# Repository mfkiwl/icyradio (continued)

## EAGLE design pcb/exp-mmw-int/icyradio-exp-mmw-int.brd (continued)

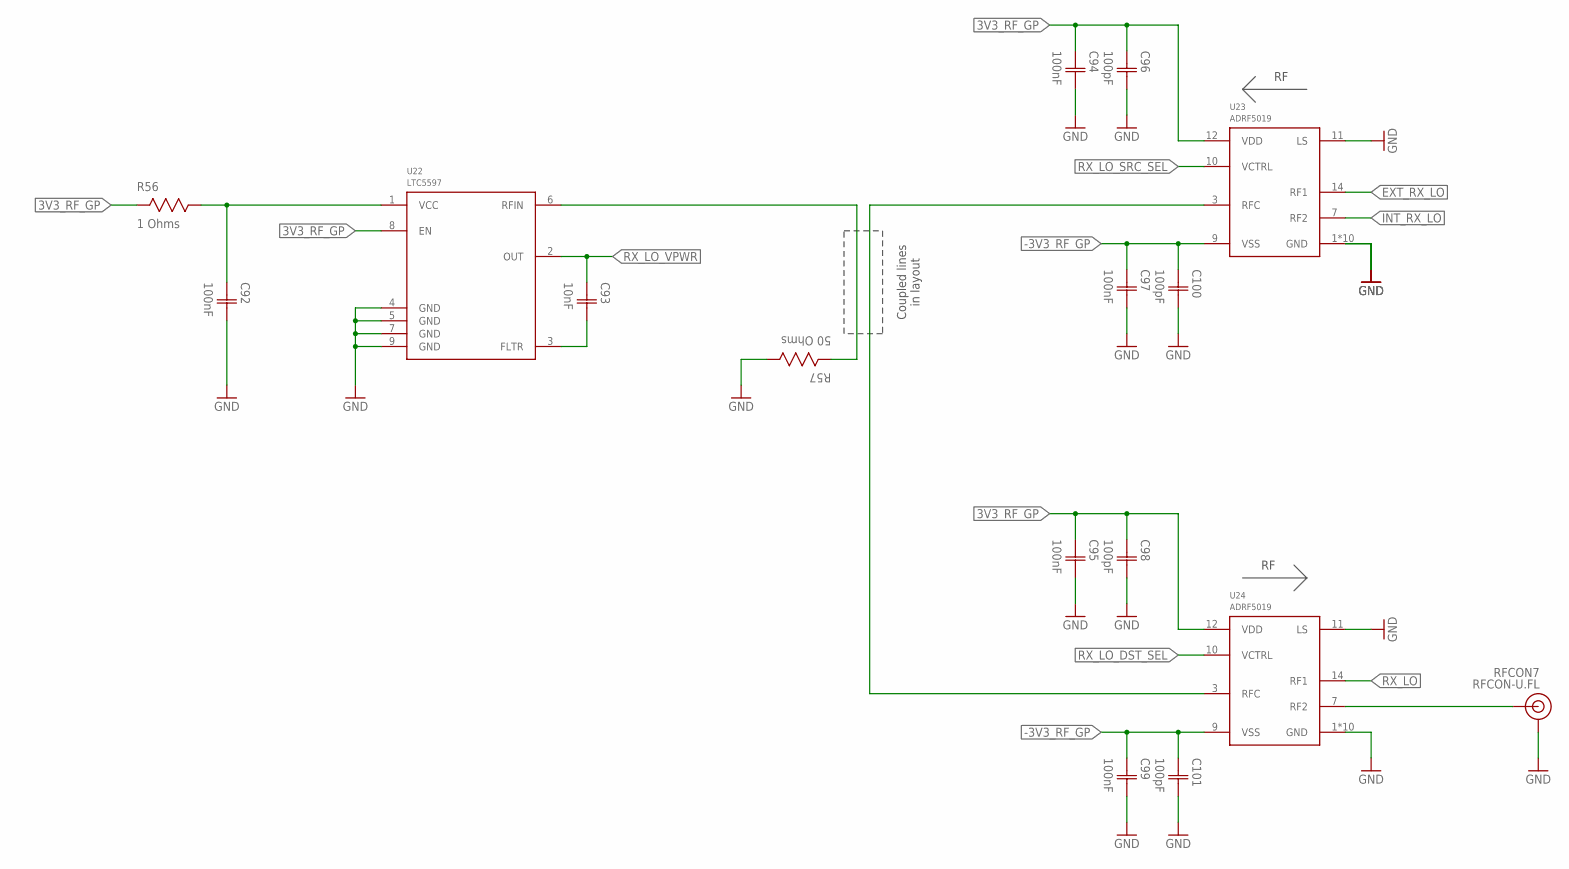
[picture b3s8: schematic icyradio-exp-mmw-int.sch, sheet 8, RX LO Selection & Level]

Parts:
C92, C94, C95, C97, C99: 100nF; CAP0402
C93: 10nF; CAP0402
C96, C98, C100, C101: 100pF; CAP0402
R56: 1 Ohms; RES0402
R57: 50 Ohms; RES0402
RFCON7: RFCON-U.FL; U.FL
U22: LTC5597; DFN8_2X2
U23, U24: ADRF5019; LFCSP16

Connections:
3V3_RF_GP: C94.1 (C1), C95.1 (C1), C96.1 (C1), C98.1 (C1), R56.2, U22.8 (EN), U23.12 (VDD), U24.12 (VDD); also elsewhere on the board
-3V3_RF_GP: C97.1 (C1), C99.1 (C1), C100.1 (C1), C101.1 (C1), U23.9 (VSS), U24.9 (VSS); also elsewhere on the board
EXT_RX_LO: U23.14 (RF1); also elsewhere on the board
GND: C92.2 (C2), C94.2 (C2), C95.2 (C2), C96.2 (C2), C97.2 (C2), C98.2 (C2), C99.2 (C2), C100.2 (C2), C101.2 (C2), R57.1, RFCON7.P$1 (GND), RFCON7.P$2 (GND), U22.4 (GND), U22.5 (GND), U22.7 (GND), U22.9 (GND), U23.1 (GND), U23.2 (GND), U23.4 (GND), U23.5 (GND), U23.6 (GND), U23.8 (GND), U23.11 (LS), U23.13 (GND), U23.15 (GND), U23.16 (GND), U23.17 (GND), U24.1 (GND), U24.2 (GND), U24.4 (GND), U24.5 (GND), U24.6 (GND), U24.8 (GND), U24.11 (LS), U24.13 (GND), U24.15 (GND), U24.16 (GND), U24.17 (GND); also elsewhere on the board
INT_RX_LO: U23.7 (RF2); also elsewhere on the board
unnamed: C93.2 (C2), U22.3 (FLTR)
unnamed: C92.1 (C1), R56.1, U22.1 (VCC)
RX_LO: U24.14 (RF1); also elsewhere on the board
RX_LO_DST_SEL: U24.10 (VCTRL); also elsewhere on the board
RX_LO_MON: RFCON7.P$3 (SIGNAL), U24.7 (RF2)
RX_LO_SNS: R57.2, U22.6 (RFIN)
RX_LO_SRC_SEL: U23.10 (VCTRL); also elsewhere on the board
RX_LO_VPWR: C93.1 (C1), U22.2 (OUT); also elsewhere on the board
SEL_RX_LO: U23.3 (RFC), U24.3 (RFC)

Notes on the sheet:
Coupled lines in layout

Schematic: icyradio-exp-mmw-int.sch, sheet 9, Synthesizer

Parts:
C102, C103, C104, C105, C106, C107, C108, C110, C111: 100nF; CAP0402
C109, C112, C113, C114, C115: 22uF; CAP0402
C116, C117: 1uF; CAP0402
C118, C120, C121, C124, C125, C126, C127: 10nF; CAP0402
C119: 2.2nF; CAP0402
C122, C123: 10pF; CAP0402
FB3: 1uH; IND0603
L5, L6: 18nH; IND0402
R58: 49.9 Ohms; RES0402
R59, R60, R61, R62: 1K Ohms; RES0402
R63: 20 Ohms; RES0402
R64: 62 Ohms; RES0402
R65, R66, R67, R68, R69, R70: 50 Ohms; RES0402
U25: 8V97003; VFQFPN48

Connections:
3V3_SYNTH: C103.1 (C1), C104.1 (C1), C105.1 (C1), C107.1 (C1), C108.1 (C1), C110.1 (C1), C111.1 (C1), FB3.1, L5.1, L6.1, R59.2, R61.2, U25.3 (VDDVCO2), U25.12 (VDDPDCP), U25.15 (VDDFB), U25.24 (VDDIN), U25.33 (VDDVCO1), U25.37 (VDDOUTA), U25.48 (VDDOUTB); also elsewhere on the board
!SYNTH_RESET: U25.31 (!RESET); also elsewhere on the board
!SYNTH_SPI_CS: U25.25 (!CS); also elsewhere on the board
GND: C103.2 (C2), C104.2 (C2), C105.2 (C2), C106.2 (C2), C107.2 (C2), C108.2 (C2), C109.2 (C2), C110.2 (C2), C111.2 (C2), C112.2 (C2), C113.2 (C2), C114.2 (C2), C115.2 (C2), C116.2 (C2), C117.2 (C2), C118.2 (C2), C119.2 (C2), C120.2 (C2), C121.2 (C2), C122.2 (C2), C123.2 (C2), R58.1, R60.1, R62.1, R69.1, R70.1, U25.14 (VSSPDCP), U25.17 (VSSFB), U25.19 (VSSDIG), U25.20 (VSSIN), U25.38 (VSSOUTA), U25.41 (VSSOUTA), U25.44 (VSSOUTB), U25.47 (VSSOUTB), U25.49 (VSS); also elsewhere on the board
INT_RX_LO: C127.2 (C2); also elsewhere on the board
INT_TX_LO: C126.2 (C2); also elsewhere on the board
unnamed: C117.1 (C1), R63.1
SYNTH_CE: U25.29 (CE); also elsewhere on the board
SYNTH_CPBIAS: C115.1 (C1), U25.11 (CPBIAS)
SYNTH_CPOUT: C118.1 (C1), R63.2, R64.2, U25.10 (CPOUT)
SYNTH_LD: U25.8 (LD); also elsewhere on the board
SYNTH_MUTE: U25.7 (MUTE); also elsewhere on the board
SYNTH_REFIN_N: C106.1 (C1), R61.1, R62.2, U25.23 (!REF_IN)
SYNTH_REFIN_P: C102.2 (C2), R59.1, R60.2, U25.22 (REF_IN)
SYNTH_REF_CLK: C102.1 (C1), R58.2; also elsewhere on the board
SYNTH_RFOUTA_ACC_N: C124.2 (C2), R69.2
SYNTH_RFOUTA_BIAS: C120.1 (C1), C122.1 (C1), L5.2, R65.2, R67.2
SYNTH_RFOUTA_N: C124.1 (C1), R67.1, U25.39 (!RF_OUTA)
SYNTH_RFOUTA_P: C126.1 (C1), R65.1, U25.40 (RF_OUTA)
SYNTH_RFOUTB_ACC_N: C125.2 (C2), R70.2
SYNTH_RFOUTB_BIAS: C121.1 (C1), C123.1 (C1), L6.2, R66.2, R68.2
SYNTH_RFOUTB_N: C125.1 (C1), R68.1, U25.46 (!RF_OUTB)
SYNTH_RFOUTB_P: C127.1 (C1), R66.1, U25.45 (RF_OUTB)
SYNTH_SPI_MISO: U25.27 (SDO); also elsewhere on the board
SYNTH_SPI_MOSI: U25.28 (SDIO); also elsewhere on the board
SYNTH_SPI_SCK: U25.26 (SCLK); also elsewhere on the board
SYNTH_SYNC: U25.30 (SYNC); also elsewhere on the board
SYNTH_VDDDIG: C116.1 (C1), FB3.2, U25.18 (VDDDIG)
SYNTH_VREFVCO1: C113.1 (C1), U25.35 (VREFVCO1)
SYNTH_VREFVCO2: C114.1 (C1), U25.1 (VREFVCO2)
SYNTH_VREGVCO1: C109.1 (C1), U25.32 (VREGVCO1)
SYNTH_VREGVCO2: C112.1 (C1), U25.4 (VREGVCO2)
SYNTH_VTUNE: C119.1 (C1), R64.1, U25.5 (VTUNE)

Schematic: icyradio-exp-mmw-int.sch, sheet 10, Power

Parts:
C128: 10uF; CAP0603
C129, C130, C131, C137, C138, C139, C143, C145: 1uF; CAP0402
C132, C133, C134, C144, C147: 100nF; CAP0402
C135, C136: 10nF; CAP0402
C140, C141, C142, C146: 10uF; CAP0402
C148: 10pF; CAP0402
R71, R72, R73: 10K Ohms; RES0402
U26: ADP7142AUJZ-3.3; SOT23-5
U27: ADM7170ACPZ-5.0; LFCSP8_3X3
U28: ADM7172ACPZ-3.3; LFCSP8_3X3
U29: ADM8828; SOT23-6

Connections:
3V3_RF_GP: C137.1 (C1), C140.1 (C1), C143.1 (C1), C144.1 (C1), U26.4 (SENSE/ADJ), U26.5 (VOUT), U29.2 (IN); also elsewhere on the board
3V3_SYNTH: C139.1 (C1), C142.1 (C1), U28.1 (VOUT), U28.2 (VOUT), U28.3 (SENSE); also elsewhere on the board
5V0: C128.1 (C1), C129.1 (C1), C130.1 (C1), C131.1 (C1), C132.1 (C1), C133.1 (C1), C134.1 (C1), U26.1 (VIN), U27.7 (VIN), U27.8 (VIN), U28.7 (VIN), U28.8 (VIN); also elsewhere on the board
5V0_RF_LO: C138.1 (C1), C141.1 (C1), U27.1 (VOUT), U27.2 (VOUT), U27.3 (SENSE); also elsewhere on the board
-3V3_RF_GP: C146.1 (C1), C147.1 (C1), C148.1 (C1), U29.1 (OUT); also elsewhere on the board
GND: C128.2 (C2), C129.2 (C2), C130.2 (C2), C131.2 (C2), C132.2 (C2), C133.2 (C2), C134.2 (C2), C135.2 (C2), C136.2 (C2), C137.2 (C2), C138.2 (C2), C139.2 (C2), C140.2 (C2), C141.2 (C2), C142.2 (C2), C143.2 (C2), C144.2 (C2), C146.2 (C2), C147.2 (C2), C148.2 (C2), R71.1, R72.1, R73.1, U26.2 (GND), U27.6 (GND), U27.9 (GND), U28.6 (GND), U28.9 (GND), U29.4 (GND), U29.5 (SHDN); also elsewhere on the board
LO_ANA_PWR_EN: R71.2, U27.5 (EN); also elsewhere on the board
unnamed: C135.1 (C1), U27.4 (SS)
unnamed: C136.1 (C1), U28.4 (SS)
unnamed: C145.1 (C1), U29.6 (C+)
unnamed: C145.2 (C2), U29.3 (C-)
RF_GP_PWR_EN: R73.2, U26.3 (EN); also elsewhere on the board
SYNTH_PWR_EN: R72.2, U28.5 (EN); also elsewhere on the board

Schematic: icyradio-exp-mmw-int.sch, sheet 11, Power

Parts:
C149, C162: 10uF; CAP0603
C150, C151, C152, C156, C157, C158, C163, C164, C169, C170: 1uF; CAP0402
C153, C154, C155, C165, C166: 100nF; CAP0402
C159, C160, C161, C171, C172: 10uF; CAP0402
C167, C168: 10nF; CAP0402
JP3: PINHD-2X3; 2X03
R74: 0 Ohms; RES0402
R75, R76, R77, R78: 10K Ohms; RES0402
U30, U31: ADP7142AUJZ-1.8; SOT23-5
U32: ADP7102ACPZ-1.5; LFCSP8_3X3
U33, U34: ADM7171ACPZ-3.3; LFCSP8_3X3

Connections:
1V5_RF_RX: C158.1 (C1), C161.1 (C1), U32.1 (VOUT), U32.2 (SENSE); also elsewhere on the board
1V8_RF_RX: C157.1 (C1), C160.1 (C1), R74.2, U31.4 (SENSE/ADJ), U31.5 (VOUT); also elsewhere on the board
1V8_RF_TX: C156.1 (C1), C159.1 (C1), R74.1, U30.4 (SENSE/ADJ), U30.5 (VOUT); also elsewhere on the board
2V5: JP3.2
3V3: C149.1 (C1), C150.1 (C1), C151.1 (C1), C153.1 (C1), C154.1 (C1), JP3.1, U30.1 (VIN), U31.1 (VIN); also elsewhere on the board
3V3_RF_RX: C170.1 (C1), C172.1 (C1), U34.1 (VOUT), U34.2 (VOUT), U34.3 (SENSE); also elsewhere on the board
3V3_RF_TX: C169.1 (C1), C171.1 (C1), U33.1 (VOUT), U33.2 (VOUT), U33.3 (SENSE); also elsewhere on the board
5V0: C152.1 (C1), C155.1 (C1), C162.1 (C1), C163.1 (C1), C164.1 (C1), C165.1 (C1), C166.1 (C1), JP3.5, JP3.6, U32.8 (VIN), U33.7 (VIN), U33.8 (VIN), U34.7 (VIN), U34.8 (VIN); also elsewhere on the board
GND: C149.2 (C2), C150.2 (C2), C151.2 (C2), C152.2 (C2), C153.2 (C2), C154.2 (C2), C155.2 (C2), C156.2 (C2), C157.2 (C2), C158.2 (C2), C159.2 (C2), C160.2 (C2), C161.2 (C2), C162.2 (C2), C163.2 (C2), C164.2 (C2), C165.2 (C2), C166.2 (C2), C167.2 (C2), C168.2 (C2), C169.2 (C2), C170.2 (C2), C171.2 (C2), C172.2 (C2), JP3.3, JP3.4, R75.1, R76.1, R77.1, R78.1, U30.2 (GND), U31.2 (GND), U32.3 (GND), U32.6 (GND), U32.9 (GND), U33.6 (GND), U33.9 (GND), U34.6 (GND), U34.9 (GND); also elsewhere on the board
unnamed: C168.1 (C1), U34.4 (SS)
unnamed: C167.1 (C1), U33.4 (SS)
RX_ANA_PWR_EN: R75.2, U32.5 (EN/UVLO), U34.5 (EN); also elsewhere on the board
RX_DIG_PWR_EN: R77.2, U31.3 (EN); also elsewhere on the board
TX_ANA_PWR_EN: R76.2, U33.5 (EN); also elsewhere on the board
TX_DIG_PWR_EN: R78.2, U30.3 (EN); also elsewhere on the board

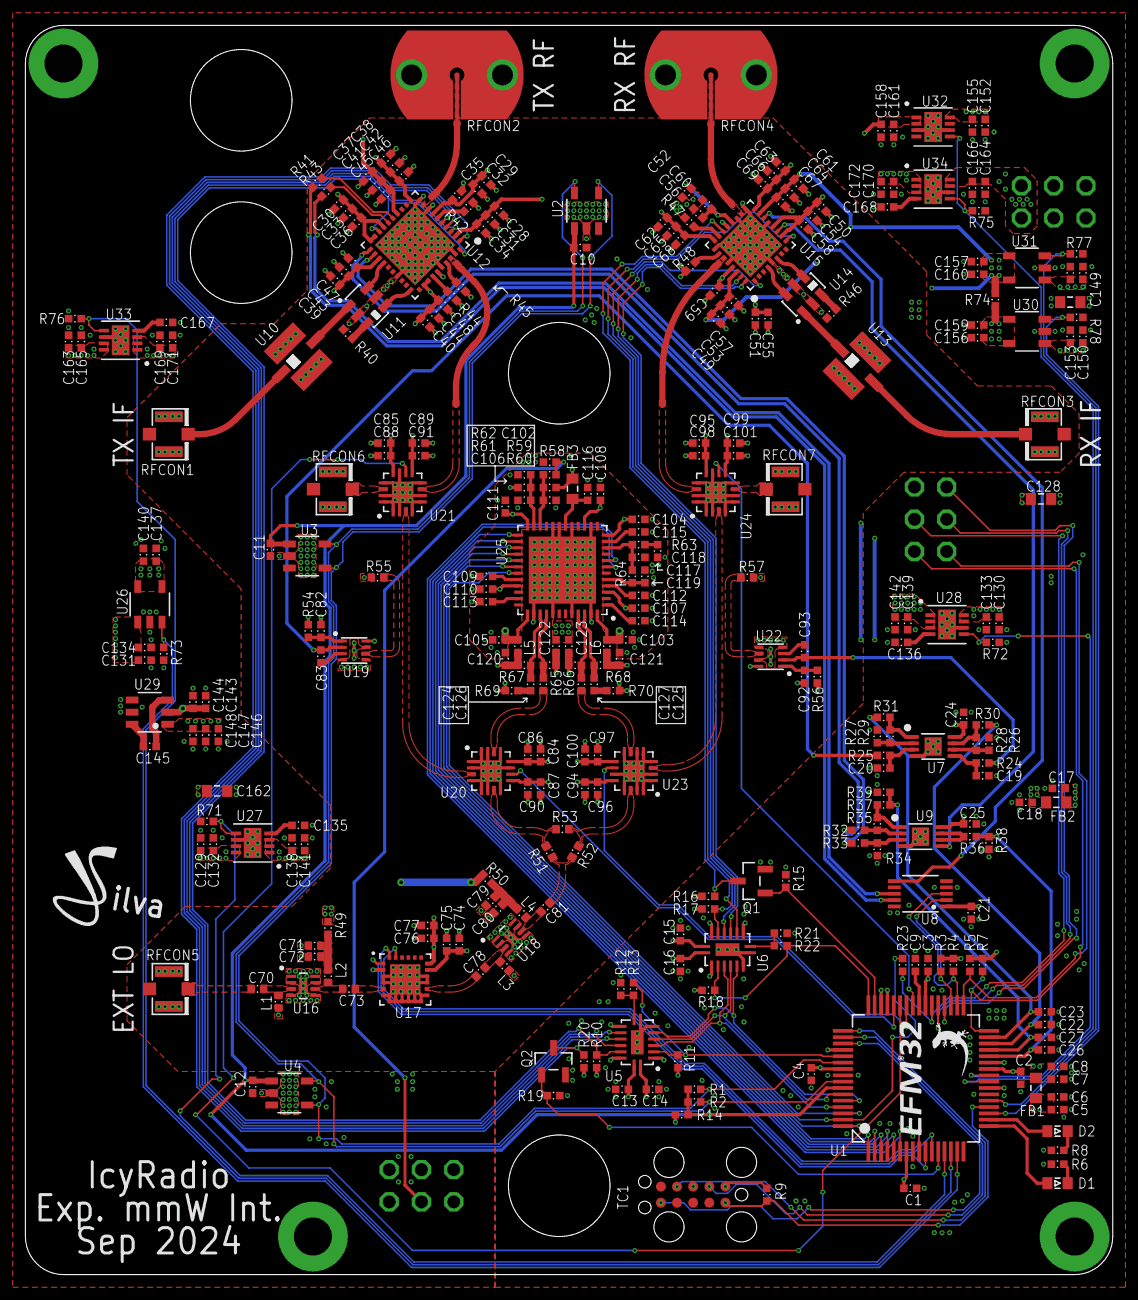
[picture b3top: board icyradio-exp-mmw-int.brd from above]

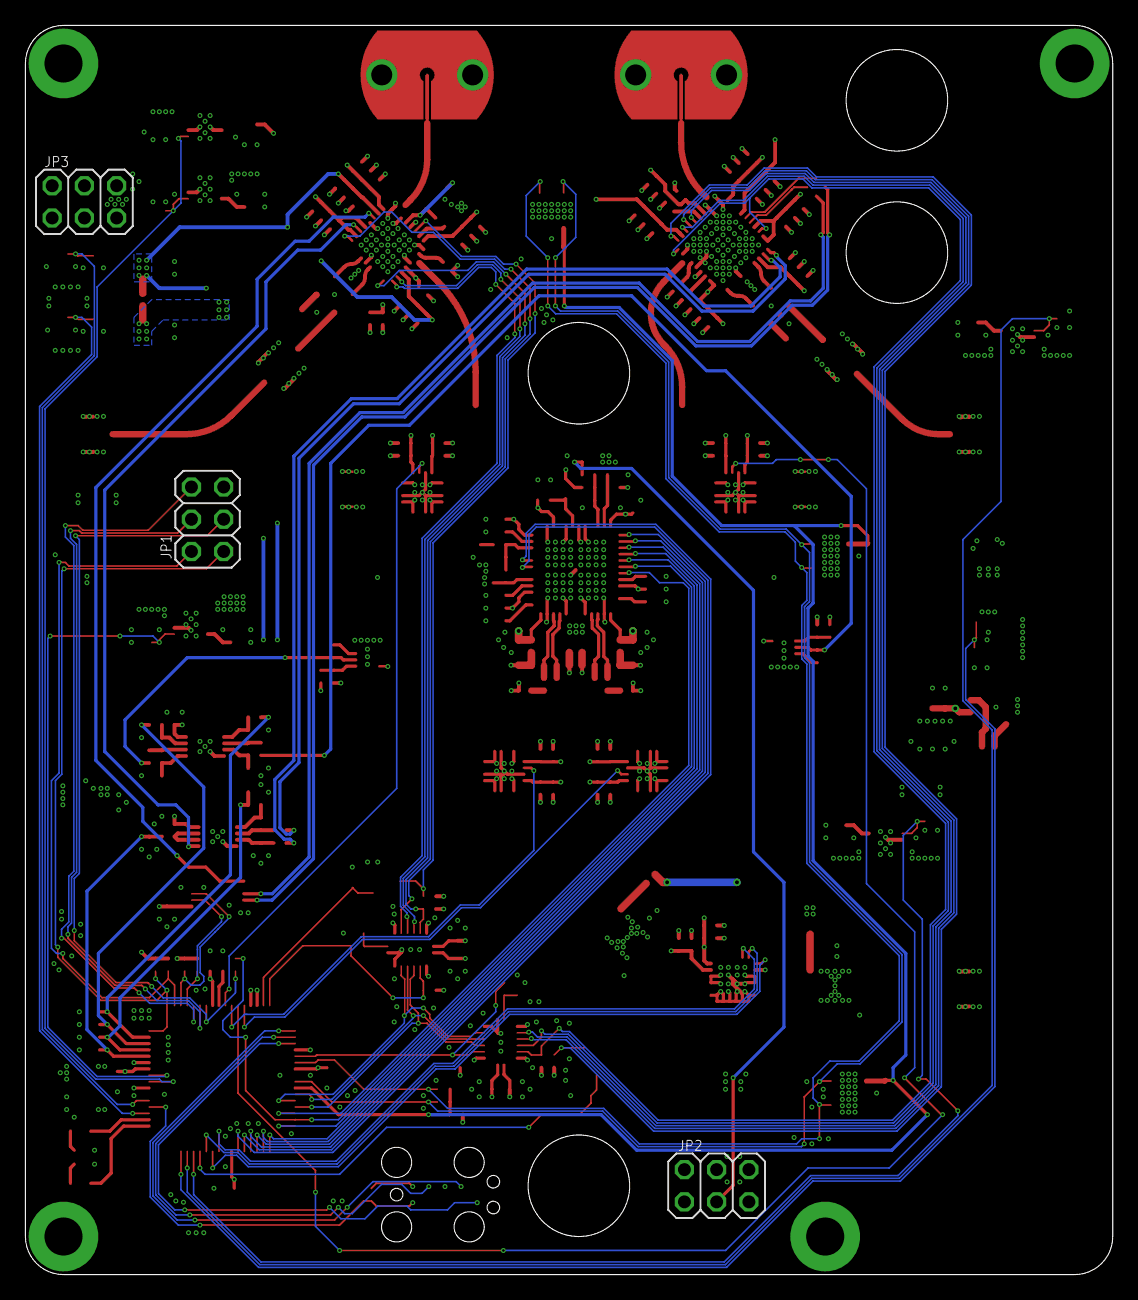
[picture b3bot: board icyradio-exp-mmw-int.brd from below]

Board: 4 copper layers, 85.7 x 98.4 mm, 309 parts (3 on the bottom side), 168 nets.

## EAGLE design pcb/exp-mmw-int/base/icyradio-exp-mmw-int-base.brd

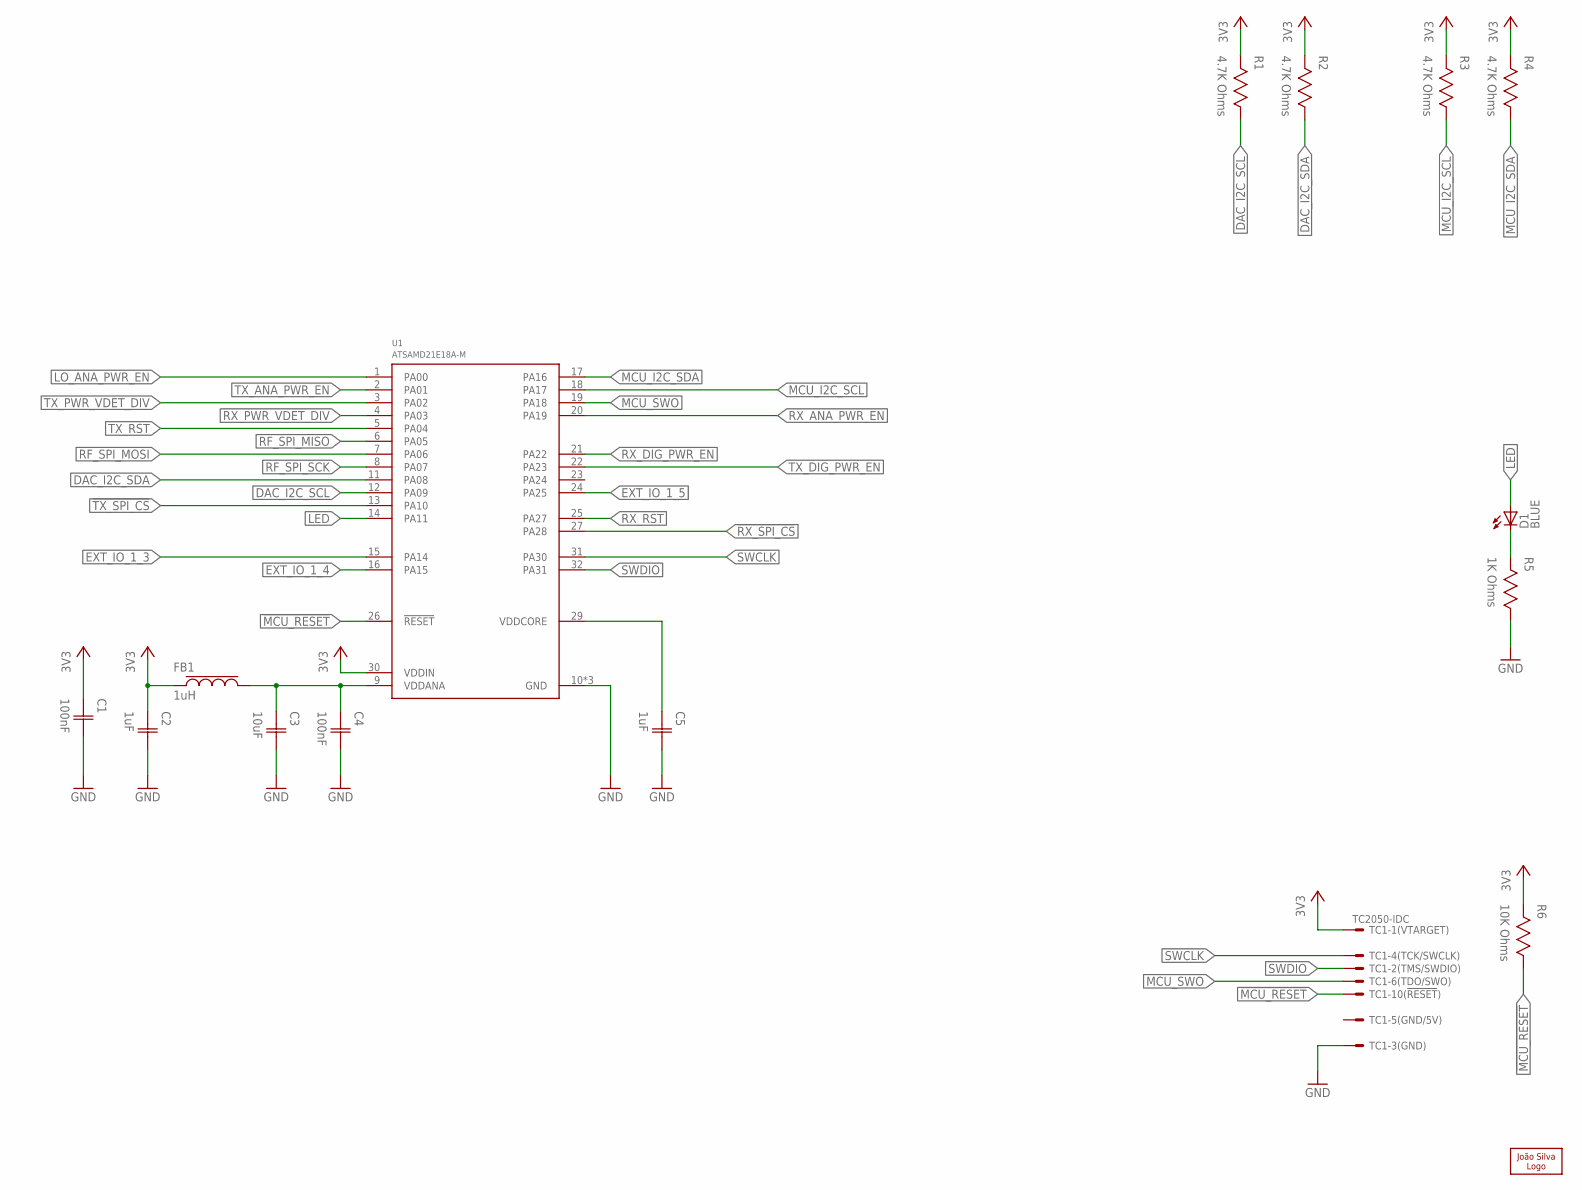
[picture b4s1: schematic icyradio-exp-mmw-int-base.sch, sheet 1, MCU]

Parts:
C1, C4: 100nF; CAP0402
C2, C5: 1uF; CAP0402
C3: 10uF; CAP0402
D1: LED0603; 0603
FB1: 1uH; IND0603
LOGO1: JSILVA-5MM; JSILVA_5MM
R1, R2, R3, R4: 4.7K Ohms; RES0402
R5: 1K Ohms; RES0402
R6: 10K Ohms; RES0402
TC1: TC2050-IDC
U1: ATSAMD21E18A-M; QFN32

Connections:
3V3: C1.1 (C1), C2.1 (C1), FB1.1, R1.2, R2.2, R3.2, R4.2, R6.2, TC1.1, U1.30 (VDDIN); also elsewhere on the board
!MCU_RESET: R6.1, TC1.10, U1.26 (!RESET)
!RX_SPI_CS: U1.27 (PA28); also elsewhere on the board
!TX_SPI_CS: U1.13 (PA10); also elsewhere on the board
DAC_I2C_SCL: R1.1, U1.12 (PA09); also elsewhere on the board
DAC_I2C_SDA: R2.1, U1.11 (PA08); also elsewhere on the board
EXT_IO_1_3: U1.15 (PA14); also elsewhere on the board
EXT_IO_1_4: U1.16 (PA15); also elsewhere on the board
EXT_IO_1_5: U1.24 (PA25); also elsewhere on the board
GND: C1.2 (C2), C2.2 (C2), C3.2 (C2), C4.2 (C2), C5.2 (C2), R5.1, TC1.3, U1.10 (GND), U1.28 (GND), U1.33 (GND); also elsewhere on the board
LED: D1.A, U1.14 (PA11)
LO_ANA_PWR_EN: U1.1 (PA00); also elsewhere on the board
MCU_I2C_SCL: R3.1, U1.18 (PA17); also elsewhere on the board
MCU_I2C_SDA: R4.1, U1.17 (PA16); also elsewhere on the board
MCU_SWO: TC1.6, U1.19 (PA18)
MCU_VDDANA: C3.1 (C1), C4.1 (C1), FB1.2, U1.9 (VDDANA)
unnamed: C5.1 (C1), U1.29 (VDDCORE)
unnamed: D1.C, R5.2
RF_SPI_MISO: U1.6 (PA05); also elsewhere on the board
RF_SPI_MOSI: U1.7 (PA06); also elsewhere on the board
RF_SPI_SCK: U1.8 (PA07); also elsewhere on the board
RX_ANA_PWR_EN: U1.20 (PA19); also elsewhere on the board
RX_DIG_PWR_EN: U1.21 (PA22); also elsewhere on the board
RX_PWR_VDET_DIV: U1.4 (PA03); also elsewhere on the board
RX_RST: U1.25 (PA27); also elsewhere on the board
SWCLK: TC1.4, U1.31 (PA30)
SWDIO: TC1.2, U1.32 (PA31)
TX_ANA_PWR_EN: U1.2 (PA01); also elsewhere on the board
TX_DIG_PWR_EN: U1.22 (PA23); also elsewhere on the board
TX_PWR_VDET_DIV: U1.3 (PA02); also elsewhere on the board
TX_RST: U1.5 (PA04); also elsewhere on the board

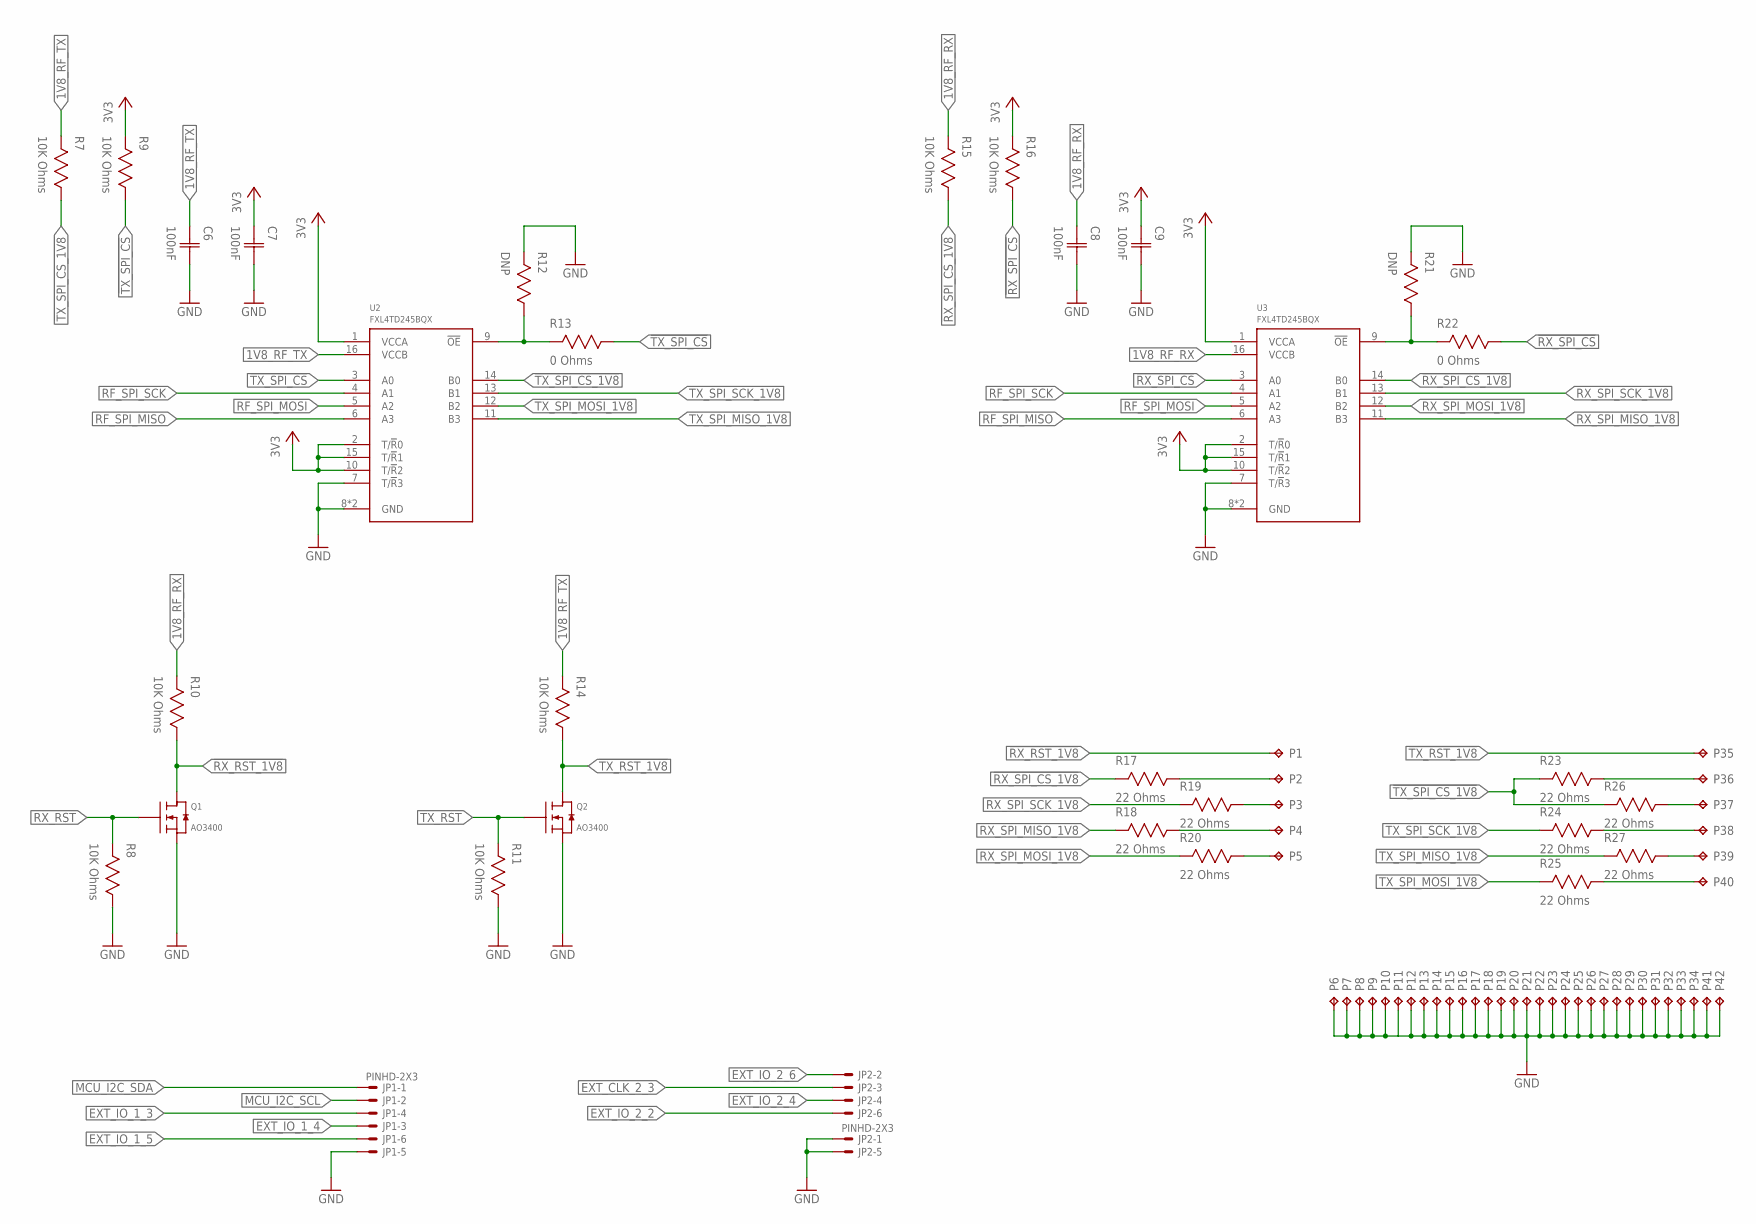
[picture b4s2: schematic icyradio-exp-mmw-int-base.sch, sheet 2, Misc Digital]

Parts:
C6, C7, C8, C9: 100nF; CAP0402
JP1, JP2: PINHD-2X3; 2X03
P1, P2, P3, P4, P5, P6, P7, P8, P9, P10, P11, P12, P13, P14, P15, P16, P17, P18, P19, P20, P21, P22, P23, P24, P25, P26, P27, P28, P29, P30, P31, P32, P33, P34, P35, P36, P37, P38, P39, P40, P41, P42: CHOLE-0.9MM-LAND; CAST_HOLE_0P9MM_LAND
Q1, Q2: AO3400; SOT23
R7, R8, R9, R10, R11, R14, R15, R16: 10K Ohms; RES0402
R12, R21: DNP; RES0402
R13, R22: 0 Ohms; RES0402
R17, R18, R19, R20, R23, R24, R25, R26, R27: 22 Ohms; RES0402
U2, U3: FXL4TD245BQX; DQFN16

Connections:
1V8_RF_RX: C8.1 (C1), R10.2, R15.2, U3.16 (VCCB); also elsewhere on the board
1V8_RF_TX: C6.1 (C1), R7.2, R14.2, U2.16 (VCCB); also elsewhere on the board
3V3: C7.1 (C1), C9.1 (C1), R9.2, R16.2, U2.1 (VCCA), U2.2 (T/!R!0), U2.10 (T/!R!2), U2.15 (T/!R!1), U3.1 (VCCA), U3.2 (T/!R!0), U3.10 (T/!R!2), U3.15 (T/!R!1); also elsewhere on the board
!RX_RST_1V8: P1.PAD_T, Q1.3 (D), R10.1
!RX_SPI_CS: R16.1, R22.1, U3.3 (A0); also elsewhere on the board
!RX_SPI_CS_1V8: R15.1, R17.2, U3.14 (B0)
!RX_SPI_OE: R21.1, R22.2, U3.9 (!OE)
!TX_RST_1V8: P35.PAD_T, Q2.3 (D), R14.1
!TX_SPI_CS: R9.1, R13.1, U2.3 (A0); also elsewhere on the board
!TX_SPI_CS_1V8: R7.1, R23.2, R26.2, U2.14 (B0)
!TX_SPI_OE: R12.1, R13.2, U2.9 (!OE)
EXT_CLK_2_3: JP2.3
EXT_IO_1_3: JP1.4; also elsewhere on the board
EXT_IO_1_4: JP1.3; also elsewhere on the board
EXT_IO_1_5: JP1.6; also elsewhere on the board
EXT_IO_2_2: JP2.6
EXT_IO_2_4: JP2.4
EXT_IO_2_6: JP2.2
GND: C6.2 (C2), C7.2 (C2), C8.2 (C2), C9.2 (C2), JP1.5, JP2.1, JP2.5, P6.PAD_T, P7.PAD_T, P8.PAD_T, P9.PAD_T, P10.PAD_T, P11.PAD_T, P12.PAD_T, P13.PAD_T, P14.PAD_T, P15.PAD_T, P16.PAD_T, P17.PAD_T, P18.PAD_T, P19.PAD_T, P20.PAD_T, P21.PAD_T, P22.PAD_T, P23.PAD_T, P24.PAD_T, P25.PAD_T, P26.PAD_T, P27.PAD_T, P28.PAD_T, P29.PAD_T, P30.PAD_T, P31.PAD_T, P32.PAD_T, P33.PAD_T, P34.PAD_T, P41.PAD_T, P42.PAD_T, Q1.2 (S), Q2.2 (S), R8.1, R11.1, R12.2, R21.2, U2.7 (T/!R!3), U2.8 (GND), U2.17 (GND), U3.7 (T/!R!3), U3.8 (GND), U3.17 (GND); also elsewhere on the board
MCU_I2C_SCL: JP1.2; also elsewhere on the board
MCU_I2C_SDA: JP1.1; also elsewhere on the board
unnamed: P2.PAD_T, R17.1
unnamed: P3.PAD_T, R19.1
unnamed: P4.PAD_T, R18.1
unnamed: P5.PAD_T, R20.1
unnamed: P37.PAD_T, R26.1
unnamed: P36.PAD_T, R23.1
unnamed: P38.PAD_T, R24.1
unnamed: P39.PAD_T, R27.1
unnamed: P40.PAD_T, R25.1
RF_SPI_MISO: U2.6 (A3), U3.6 (A3); also elsewhere on the board
RF_SPI_MOSI: U2.5 (A2), U3.5 (A2); also elsewhere on the board
RF_SPI_SCK: U2.4 (A1), U3.4 (A1); also elsewhere on the board
RX_RST: Q1.1 (G), R8.2; also elsewhere on the board
RX_SPI_MISO_1V8: R18.2, U3.11 (B3)
RX_SPI_MOSI_1V8: R20.2, U3.12 (B2)
RX_SPI_SCK_1V8: R19.2, U3.13 (B1)
TX_RST: Q2.1 (G), R11.2; also elsewhere on the board
TX_SPI_MISO_1V8: R27.2, U2.11 (B3)
TX_SPI_MOSI_1V8: R25.2, U2.12 (B2)
TX_SPI_SCK_1V8: R24.2, U2.13 (B1)

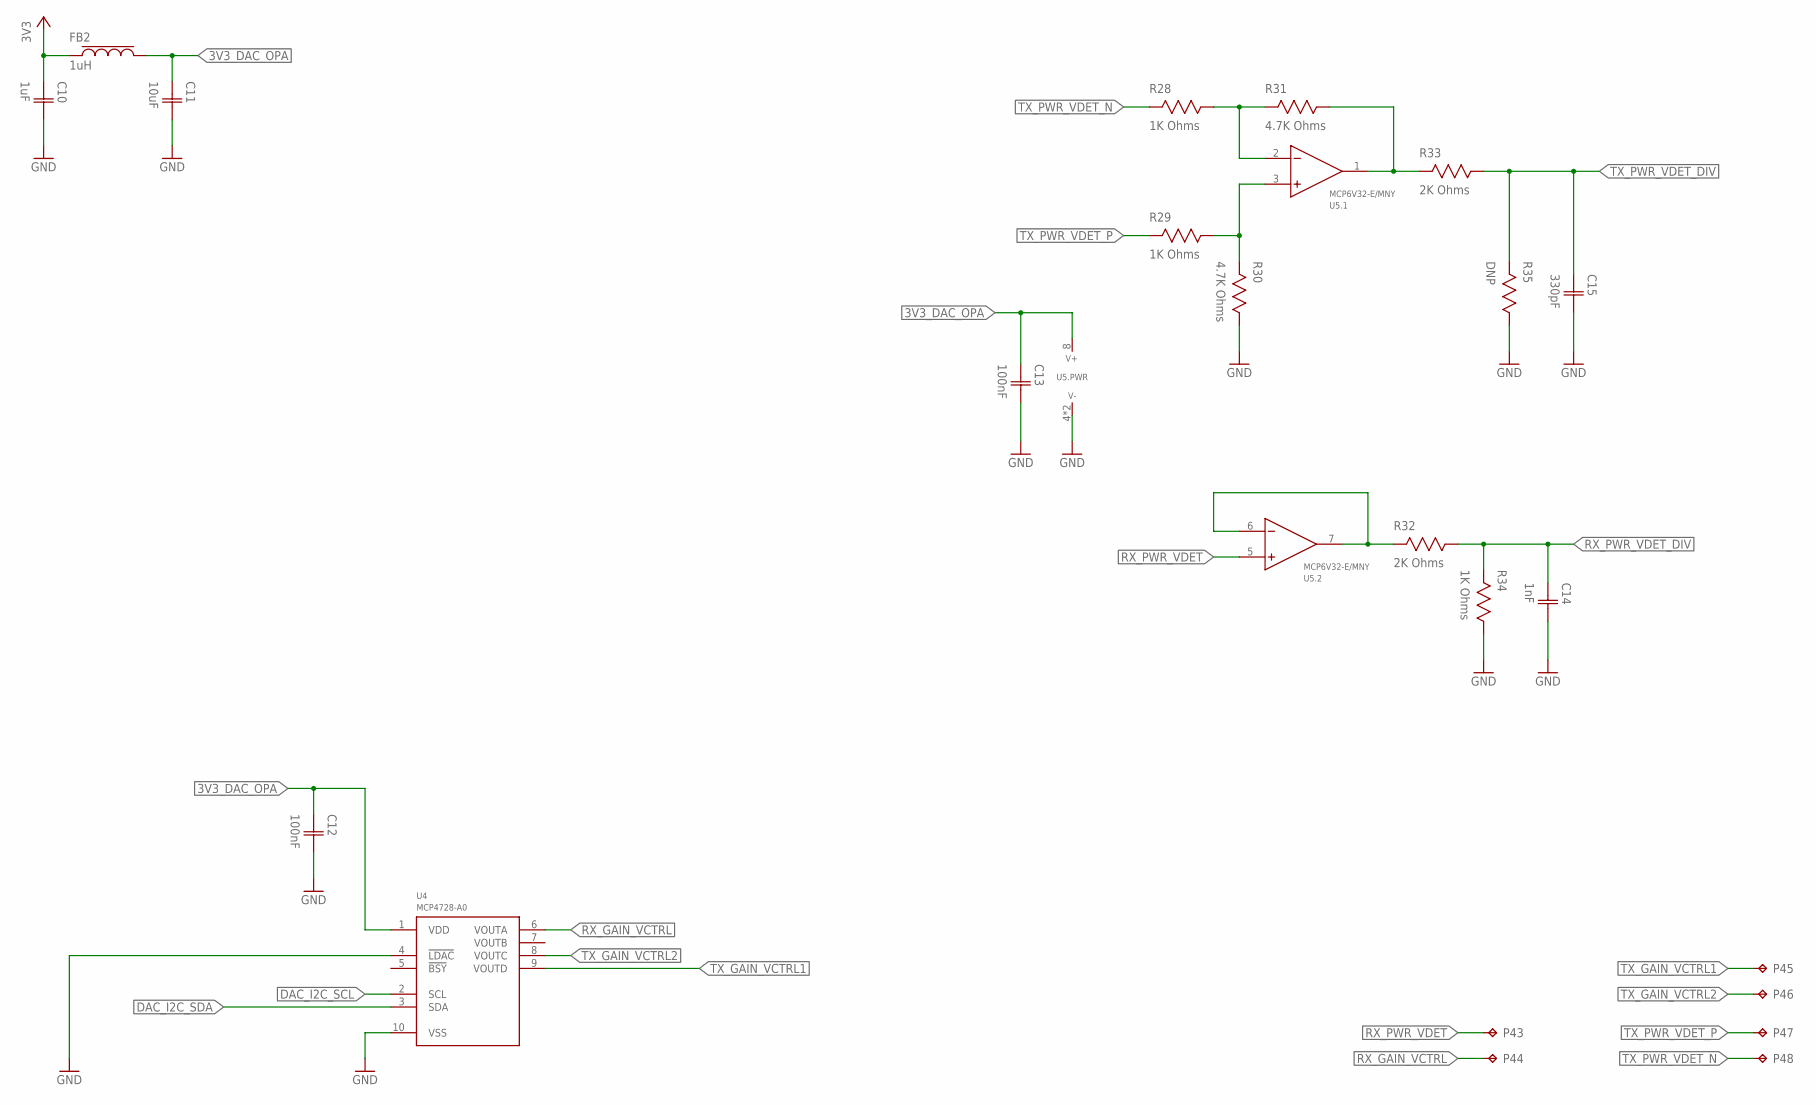
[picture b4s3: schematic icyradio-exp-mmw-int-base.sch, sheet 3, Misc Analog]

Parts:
C10: 1uF; CAP0402
C11: 10uF; CAP0402
C12, C13: 100nF; CAP0402
C14: 1nF; CAP0402
C15: 330pF; CAP0402
FB2: 1uH; IND0603
P43, P44, P45, P46, P47, P48: CHOLE-0.9MM-LAND; CAST_HOLE_0P9MM_LAND
R28, R29, R34: 1K Ohms; RES0402
R30, R31: 4.7K Ohms; RES0402
R32, R33: 2K Ohms; RES0402
R35: DNP; RES0402
U4: MCP4728-A0; MSOP10
U5: MCP6V32-E/MNY; TDFN8

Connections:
3V3: C10.1 (C1), FB2.1; also elsewhere on the board
3V3_DAC_OPA: C11.1 (C1), C12.1 (C1), C13.1 (C1), FB2.2, U4.1 (VDD), U5.8 (V+)
DAC_I2C_SCL: U4.2 (SCL); also elsewhere on the board
DAC_I2C_SDA: U4.3 (SDA); also elsewhere on the board
GND: C10.2 (C2), C11.2 (C2), C12.2 (C2), C13.2 (C2), C14.2 (C2), C15.2 (C2), R30.1, R34.1, R35.1, U4.4 (!LDAC), U4.10 (VSS), U5.4 (V-), U5.9 (V-); also elsewhere on the board
unnamed: R28.1, R31.2, U5.2 (-IN)
unnamed: R29.1, R30.2, U5.3 (+IN)
unnamed: R32.2, U5.6 (-IN), U5.7 (OUT)
RX_GAIN_VCTRL: P44.PAD_T, U4.6 (VOUTA)
RX_PWR_VDET: P43.PAD_T, U5.5 (+IN)
RX_PWR_VDET_DIV: C14.1 (C1), R32.1, R34.2; also elsewhere on the board
TX_GAIN_VCTRL1: P45.PAD_T, U4.9 (VOUTD)
TX_GAIN_VCTRL2: P46.PAD_T, U4.8 (VOUTC)
TX_PWR_VDET: R31.1, R33.2, U5.1 (OUT)
TX_PWR_VDET_DIV: C15.1 (C1), R33.1, R35.2; also elsewhere on the board
TX_PWR_VDET_N: P48.PAD_T, R28.2
TX_PWR_VDET_P: P47.PAD_T, R29.2
